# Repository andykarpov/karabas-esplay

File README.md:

# Karabas ESPlay

A derivative pcb for the ESPlay micro project.

## Key differences:

- A bigger 3.2" ILI9341 display
- Silicone buttons
- Turbo buttons (C and D)

## Credits and license

This board is derived from [ESPlay micro](https://github.com/pebri86/esplay_micro_hardware) by Fuji Pebri. That repository has no license file, but its author [states](https://github.com/pebri86/esplay_micro_hardware/issues/8) that the project is open source and free to modify and build upon, and asks to share modified versions.

The changes made in this repository are released under the MIT License, see [LICENSE](LICENSE). Rights in the original design remain with its author.

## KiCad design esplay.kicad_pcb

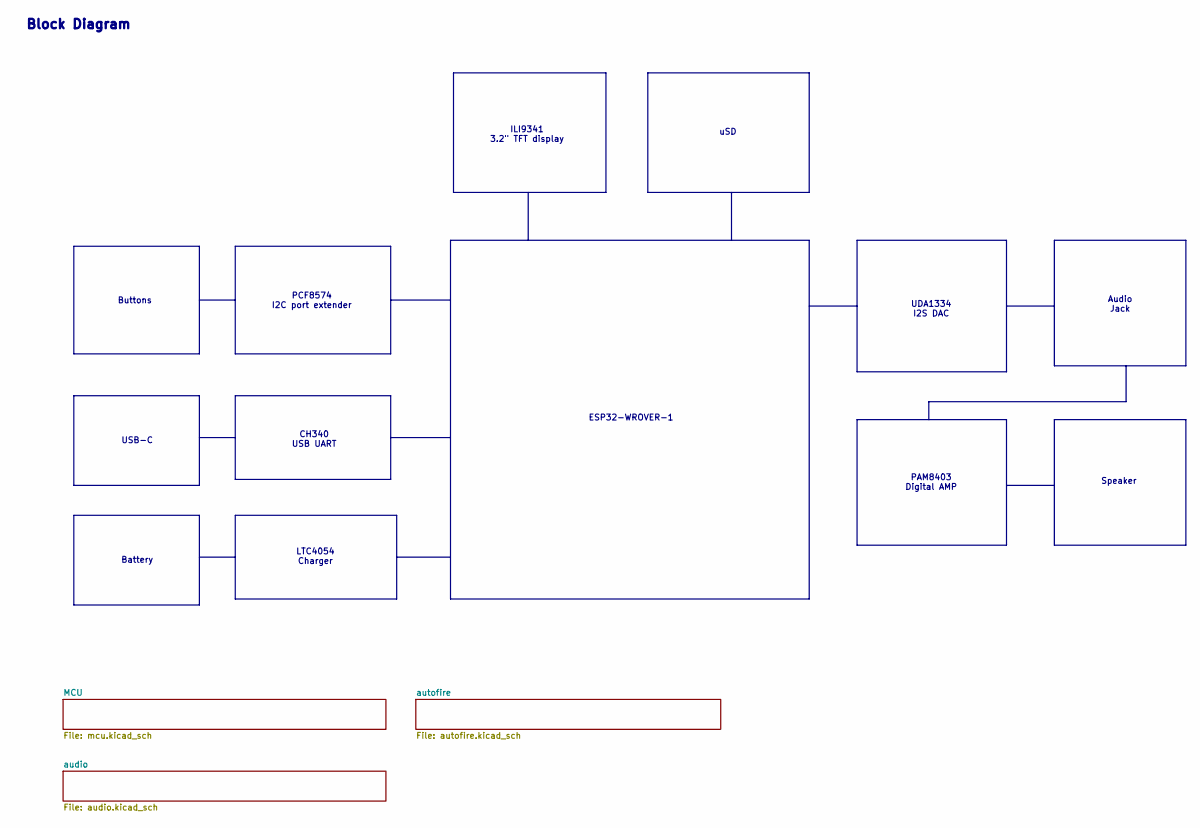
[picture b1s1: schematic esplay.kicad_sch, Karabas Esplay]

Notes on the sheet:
Block Diagram
PCF8574 I2C port extender
Audio Jack
uSD
Battery
LTC4054 Charger
UDA1334 I2S DAC
CH340 USB UART
Speaker
ILI9341 3.2" TFT display
Buttons
ESP32-WROVER-1
PAM8403 Digital AMP
USB-C

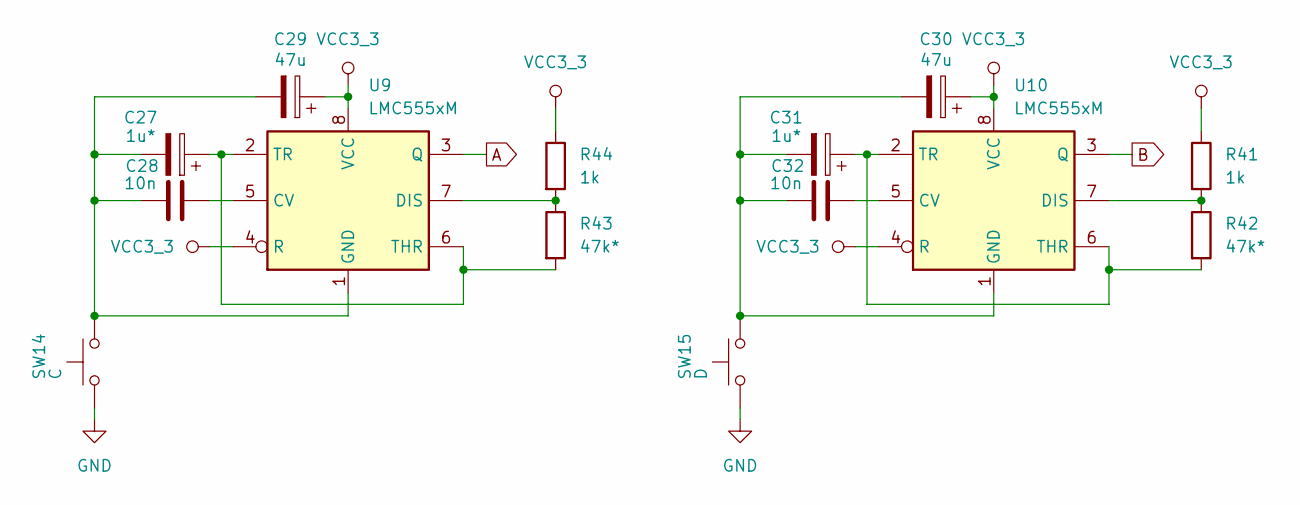
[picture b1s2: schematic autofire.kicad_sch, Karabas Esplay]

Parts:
C27, C31: 1u*; CP_EIA-3528-21_Kemet-B_HandSolder
C28, C32: 10n; C_0805_2012Metric_Pad1.18x1.45mm_HandSolder
C29, C30: 47u; CP_EIA-3528-21_Kemet-B_HandSolder
R41, R44: 1k; R_0805_2012Metric_Pad1.20x1.40mm_HandSolder
R42, R43: 47k*; R_0805_2012Metric_Pad1.20x1.40mm_HandSolder
SW14: C; SW_Push_1TS009_combined1
SW15: D; SW_Push_1TS009_combined1
U9, U10: LMC555xM; SOIC-8_3.9x4.9mm_P1.27mm

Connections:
A: U9.3 (Q); also elsewhere on the board
B: U10.3 (Q); also elsewhere on the board
GND: SW14.1, SW15.1; also elsewhere on the board
unnamed: C28.2, U9.5 (CV)
unnamed: R43.1, R44.2, U9.7 (DIS)
unnamed: C27.2, C28.1, C29.2, SW14.2, U9.1 (GND)
unnamed: C27.1, R43.2, U9.2 (TR), U9.6 (THR)
unnamed: C32.2, U10.5 (CV)
unnamed: R41.2, R42.1, U10.7 (DIS)
unnamed: C30.2, C31.2, C32.1, SW15.2, U10.1 (GND)
unnamed: C31.1, R42.2, U10.2 (TR), U10.6 (THR)
VCC3_3: C29.1, C30.1, R41.1, R44.1, U9.4 (R), U9.8 (VCC), U10.4 (R), U10.8 (VCC); also elsewhere on the board

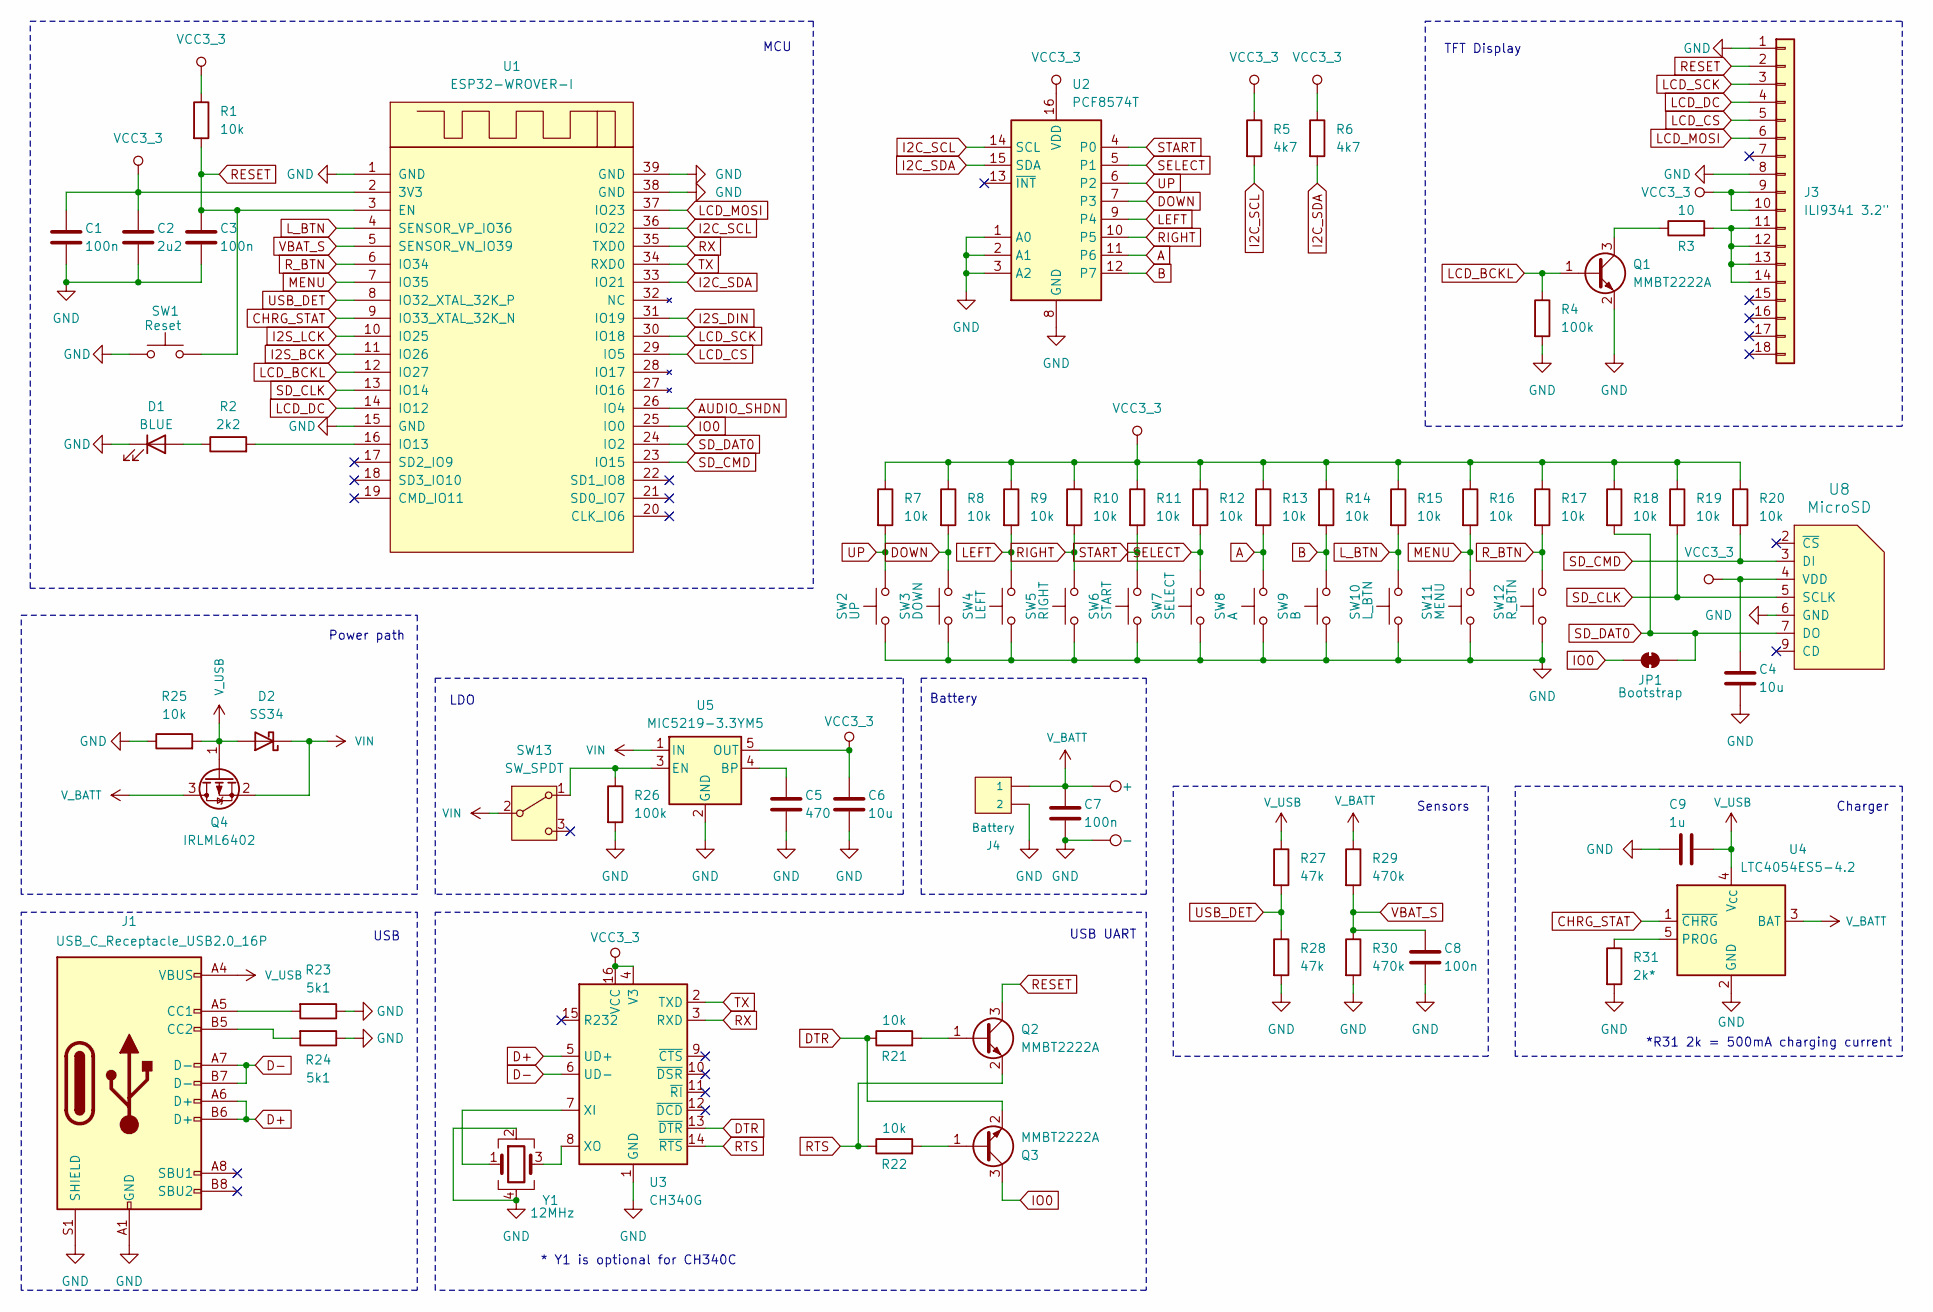
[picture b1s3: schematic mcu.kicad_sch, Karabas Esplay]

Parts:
BAT+1: +; TestPoint_Pad_D3.0mm
BAT-1: -; TestPoint_Pad_D3.0mm
C1, C3, C7, C8: 100n; C_0805_2012Metric_Pad1.18x1.45mm_HandSolder
C2: 2u2; C_0805_2012Metric_Pad1.18x1.45mm_HandSolder
C4, C6: 10u; C_0805_2012Metric_Pad1.18x1.45mm_HandSolder
C5: 470; C_0805_2012Metric_Pad1.18x1.45mm_HandSolder
C9: 1u; C_0805_2012Metric_Pad1.18x1.45mm_HandSolder
D1: BLUE; LED_0805_2012Metric_Pad1.15x1.40mm_HandSolder
D2: SS34; D_SMA
J1: USB_C_Receptacle_USB2.0_16P; USB_C_Receptacle_HRO_TYPE-C-31-M-12
J3: ILI9341 3.2"; TFT-ILI9341-3.2
J4: Battery; JST_PH_S2B-PH-K_1x02_P2.00mm_Horizontal
JP1: Bootstrap; SolderJumper-2_P1.3mm_Bridged_RoundedPad1.0x1.5mm
Q1, Q2, Q3: MMBT2222A; SOT-23
Q4: IRLML6402; SOT-23
R1, R7, R8, R9, R10, R11, R12, R13, R14, R15, R16, R17, R18, R19, R20, R21, R22, R25: 10k; R_0805_2012Metric_Pad1.20x1.40mm_HandSolder
R2: 2k2; R_0805_2012Metric_Pad1.20x1.40mm_HandSolder
R3: 10; R_0805_2012Metric_Pad1.20x1.40mm_HandSolder
R4, R26: 100k; R_0805_2012Metric_Pad1.20x1.40mm_HandSolder
R5, R6: 4k7; R_0805_2012Metric_Pad1.20x1.40mm_HandSolder
R23, R24: 5k1; R_0805_2012Metric_Pad1.20x1.40mm_HandSolder
R27, R28: 47k; R_0805_2012Metric_Pad1.20x1.40mm_HandSolder
R29, R30: 470k; R_0805_2012Metric_Pad1.20x1.40mm_HandSolder
R31: 2k*; R_0805_2012Metric_Pad1.20x1.40mm_HandSolder
SW1: Reset; SW_SPST_PTS810_handsoldering
SW2: UP; SW_Push_1TS009_combined1
SW3: DOWN; SW_Push_1TS009_combined1
SW4: LEFT; SW_Push_1TS009_combined1
SW5: RIGHT; SW_Push_1TS009_combined1
SW6: START; SW_Push_1TS009_combined1
SW7: SELECT; SW_Push_1TS009_combined1
SW8: A; SW_Push_1TS009_combined1
SW9: B; SW_Push_1TS009_combined1
SW10: L_BTN; SW_Tactile_SPST_Angled_PTS645Vx58-2LFS
SW11: MENU; SW_Push_1TS009_combined1
SW12: R_BTN; SW_Tactile_SPST_Angled_PTS645Vx58-2LFS
SW13: SW_SPDT; SW_Slide_SPDT_Angled_CK_OS102011MA1Q
U1: ESP32-WROVER-I; ESP32-WROVER
U2: PCF8574T; SOIC-16W_7.5x10.3mm_P1.27mm
U3: CH340G; SOIC-16_3.9x9.9mm_P1.27mm
U4: LTC4054ES5-4.2; TSOT-23-5
U5: MIC5219-3.3YM5; SOT-23-5
U8: MicroSD; GCT-MEM2055-00-190-01-A
Y1: 12MHz; Crystal_SMD_3225-4Pin_3.2x2.5mm_HandSoldering

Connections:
A: R13.2, SW8.2, U2.11 (P6); also elsewhere on the board
AUDIO_SHDN: U1.26 (IO4); also elsewhere on the board
B: R14.2, SW9.2, U2.12 (P7); also elsewhere on the board
CHRG_STAT: U1.9 (IO33_XTAL_32K_N), U4.1 (~CHRG)
D+: J1.A6 (D+), J1.B6 (D+), U3.5 (UD+)
D-: J1.A7 (D-), J1.B7 (D-), U3.6 (UD-)
DOWN: R8.2, SW3.2, U2.7 (P3)
DTR: Q3.2 (E), R21.1, U3.13 (~DTR)
GND: BAT-1.1, C1.2, C2.2, C3.2, C4.2, C5.2, C6.2, C7.2, C8.2, C9.1, D1.1 (K), J1.A1 (GND), J1.A12 (GND), J1.B1 (GND), J1.B12 (GND), J1.S1 (SHIELD), J3.1, J3.8, J4.2, Q1.2 (E), R4.2, R23.1, R24.1, R25.1, R26.2, R28.2, R30.2, R31.2, SW1.1, SW2.1, SW3.1, SW4.1, SW5.1, SW6.1, SW7.1, SW8.1, SW9.1, SW10.1, SW11.1, SW12.1, U1.1 (GND), U1.15 (GND), U1.38 (GND), U1.39 (GND), U2.1 (A0), U2.2 (A1), U2.3 (A2), U2.8 (GND), U3.1 (GND), U4.2 (GND), U5.2 (GND), U8.6 (GND), Y1.2, Y1.4; also elsewhere on the board
I2C_SCL: R5.2, U1.36 (IO22), U2.14 (SCL)
I2C_SDA: R6.2, U1.33 (IO21), U2.15 (SDA)
I2S_BCK: U1.11 (IO26); also elsewhere on the board
I2S_DIN: U1.31 (IO19); also elsewhere on the board
I2S_LCK: U1.10 (IO25); also elsewhere on the board
IO0: JP1.1 (A), Q3.3 (C), U1.25 (IO0)
LCD_BCKL: Q1.1 (B), R4.1, U1.12 (IO27)
LCD_CS: J3.5, U1.29 (IO5)
LCD_DC: J3.4, U1.14 (IO12)
LCD_MOSI: J3.6, U1.37 (IO23)
LCD_SCK: J3.3, U1.30 (IO18)
LEFT: R9.2, SW4.2, U2.9 (P4)
L_BTN: R15.2, SW10.2, U1.4 (SENSOR_VP_IO36)
MENU: R16.2, SW11.2, U1.7 (IO35)
unnamed: D1.2 (A), R2.1
unnamed: J1.A5 (CC1), R23.2
unnamed: J1.B5 (CC2), R24.2
unnamed: J3.11, J3.12, J3.13, J3.14, R3.2
unnamed: Q1.3 (C), R3.1
unnamed: Q2.1 (B), R21.2
unnamed: Q3.1 (B), R22.2
unnamed: R26.1, SW13.1 (A), U5.3 (EN)
unnamed: R2.2, U1.16 (IO13)
unnamed: U3.7 (XI), Y1.1
unnamed: U3.8 (XO), Y1.3
unnamed: R31.1, U4.5 (PROG)
unnamed: C5.1, U5.4 (BP)
RESET: C3.1, J3.2, Q2.3 (C), R1.2, SW1.2, U1.3 (EN)
RIGHT: R10.2, SW5.2, U2.10 (P5)
RTS: Q2.2 (E), R22.1, U3.14 (~RTS)
RX: U1.35 (TXD0), U3.3 (RXD)
R_BTN: R17.2, SW12.2, U1.6 (IO34)
SD_CLK: R19.2, U1.13 (IO14), U8.5 (SCLK)
SD_CMD: R20.2, U1.23 (IO15), U8.3 (DI)
SD_DAT0: JP1.2 (B), R18.2, U1.24 (IO2), U8.7 (DO)
SELECT: R12.2, SW7.2, U2.5 (P1)
START: R11.2, SW6.2, U2.4 (P0)
TX: U1.34 (RXD0), U3.2 (TXD)
UP: R7.2, SW2.2, U2.6 (P2)
USB_DET: R27.2, R28.1, U1.8 (IO32_XTAL_32K_P)
VBAT_S: C8.1, R29.2, R30.1, U1.5 (SENSOR_VN_IO39)
VCC3_3: C1.1, C2.1, C4.1, C6.1, J3.9, J3.10, R1.1, R5.1, R6.1, R7.1, R8.1, R9.1, R10.1, R11.1, R12.1, R13.1, R14.1, R15.1, R16.1, R17.1, R18.1, R19.1, R20.1, U1.2 (3V3), U2.16 (VDD), U3.4 (V3), U3.16 (VCC), U5.5 (OUT), U8.4 (VDD); also elsewhere on the board
VIN: D2.1 (K), Q4.2 (S), SW13.2 (B), U5.1 (IN); also elsewhere on the board
V_BATT: BAT+1.1, C7.1, J4.1, Q4.3 (D), R29.1, U4.3 (BAT)
V_USB: C9.2, D2.2 (A), J1.A4 (VBUS), J1.A9 (VBUS), J1.B4 (VBUS), J1.B9 (VBUS), Q4.1 (G), R25.2, R27.1, U4.4 (V_{CC})

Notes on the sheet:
*R31 2k = 500mA charging current
TFT Display
USB UART
USB
LDO
Charger
MCU
Battery
Sensors
* Y1 is optional for CH340C
Power path

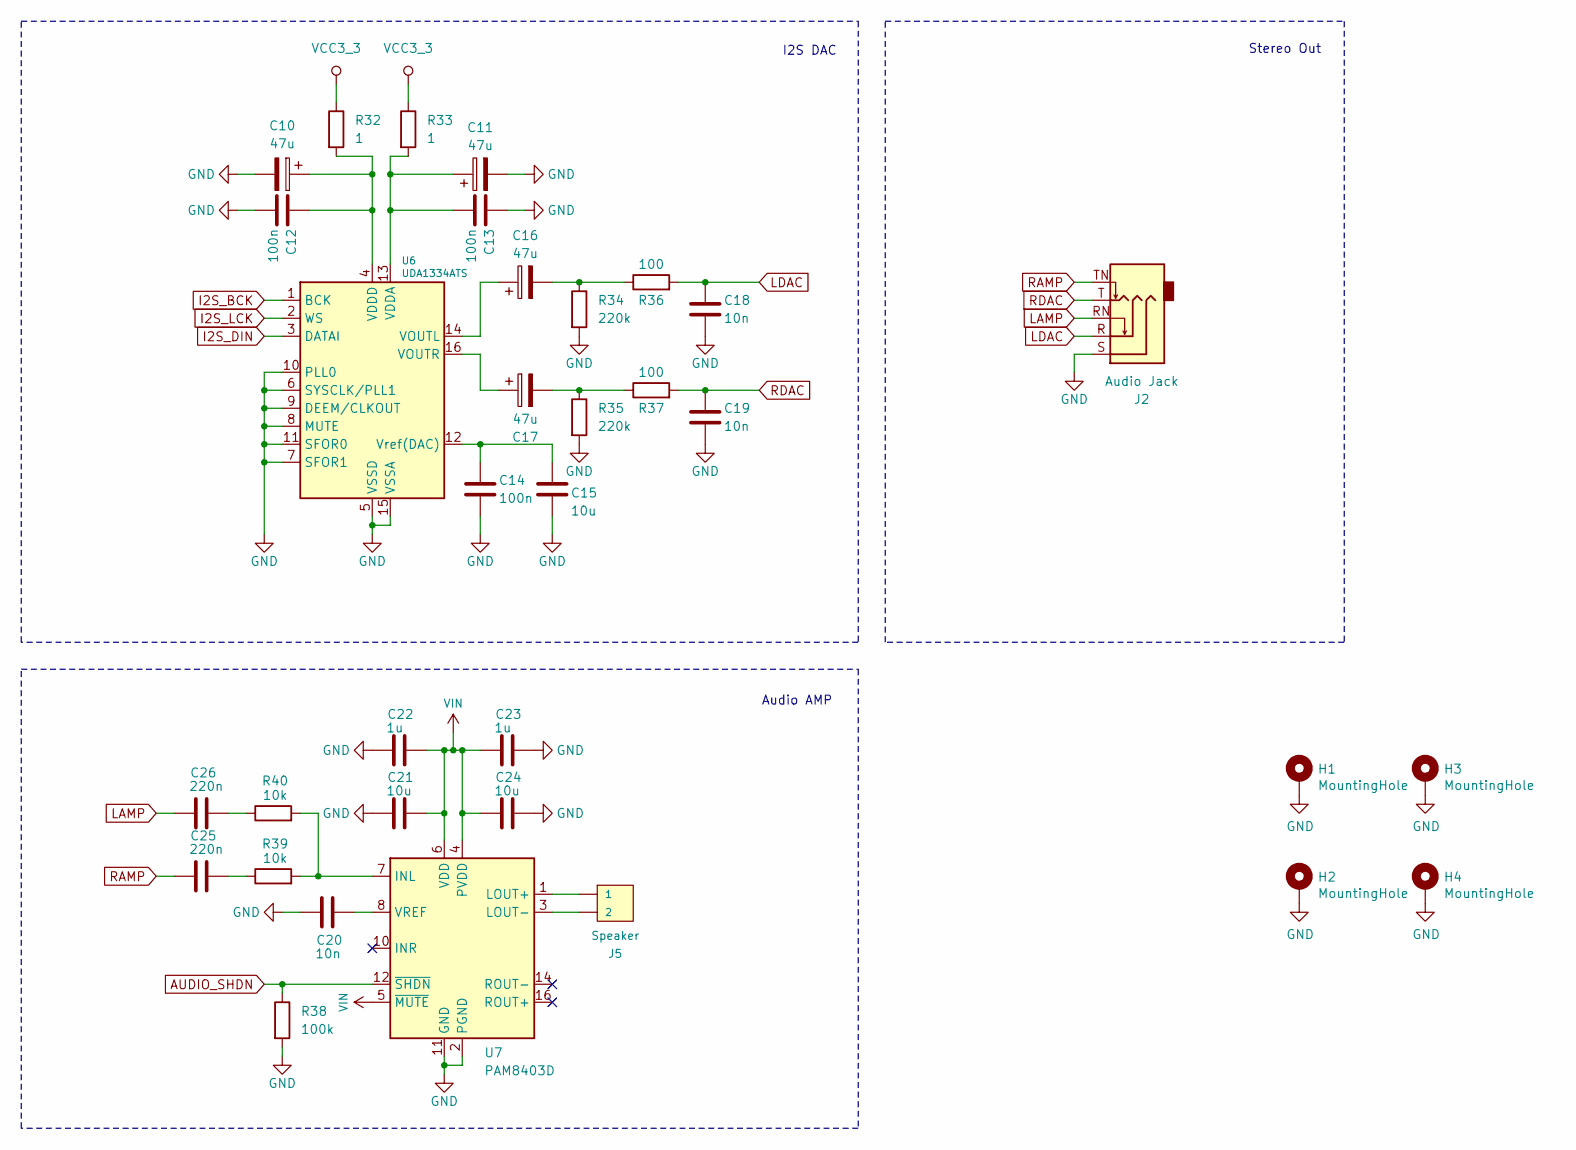
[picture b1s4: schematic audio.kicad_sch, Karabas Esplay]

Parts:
C10, C11, C16, C17: 47u; CP_EIA-3528-21_Kemet-B_HandSolder
C12, C13, C14: 100n; C_0805_2012Metric_Pad1.18x1.45mm_HandSolder
C15, C21, C24: 10u; C_0805_2012Metric_Pad1.18x1.45mm_HandSolder
C18, C19, C20: 10n; C_0805_2012Metric_Pad1.18x1.45mm_HandSolder
C22, C23: 1u; C_0805_2012Metric_Pad1.18x1.45mm_HandSolder
C25, C26: 220n; C_0805_2012Metric_Pad1.18x1.45mm_HandSolder
H1, H2, H3, H4: MountingHole; MountingHole_3.5mm_Pad_Via
J2: Audio Jack; Jack_3.5mm_CUI_SJ1-3525N_Horizontal
J5: Speaker; PinHeader_1x02_P2.54mm_Vertical
R32, R33: 1; R_0805_2012Metric_Pad1.20x1.40mm_HandSolder
R34, R35: 220k; R_0805_2012Metric_Pad1.20x1.40mm_HandSolder
R36, R37: 100; R_0805_2012Metric_Pad1.20x1.40mm_HandSolder
R38: 100k; R_0805_2012Metric_Pad1.20x1.40mm_HandSolder
R39, R40: 10k; R_0805_2012Metric_Pad1.20x1.40mm_HandSolder
U6: UDA1334ATS; SSOP-16_4.4x5.2mm_P0.65mm-extended
U7: PAM8403D; SOIC-16_3.9x9.9mm_P1.27mm

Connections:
AUDIO_SHDN: R38.1, U7.12 (~SHDN); also elsewhere on the board
GND: C10.2, C11.2, C12.2, C13.1, C14.2, C15.2, C18.2, C19.2, C20.1, C21.1, C22.1, C23.2, C24.2, H1.1, H2.1, H3.1, H4.1, J2.S, R34.2, R35.2, R38.2, U6.5 (VSSD), U6.6 (SYSCLK/PLL1), U6.7 (SFOR1), U6.8 (MUTE), U6.9 (DEEM/CLKOUT), U6.10 (PLL0), U6.11 (SFOR0), U6.15 (VSSA), U7.2 (PGND), U7.11 (GND), U7.15 (PGND); also elsewhere on the board
I2S_BCK: U6.1 (BCK); also elsewhere on the board
I2S_DIN: U6.3 (DATAI); also elsewhere on the board
I2S_LCK: U6.2 (WS); also elsewhere on the board
LAMP: C26.2, J2.RN
LDAC: C18.1, J2.R, R36.2
unnamed: C16.2, R34.1, R36.1
unnamed: C17.2, R35.1, R37.1
unnamed: C25.1, R39.1
unnamed: C26.1, R40.1
unnamed: C11.1, C13.2, R33.2, U6.13 (VDDA)
unnamed: C10.1, C12.1, R32.2, U6.4 (VDDD)
unnamed: C16.1, U6.14 (VOUTL)
unnamed: C17.1, U6.16 (VOUTR)
unnamed: C14.1, C15.1, U6.12 (Vref(DAC))
unnamed: R39.2, R40.2, U7.7 (INL)
unnamed: J5.1, U7.1 (LOUT+)
unnamed: J5.2, U7.3 (LOUT-)
unnamed: C20.2, U7.8 (VREF)
RAMP: C25.2, J2.TN
RDAC: C19.1, J2.T, R37.2
VCC3_3: R32.1, R33.1; also elsewhere on the board
VIN: C21.2, C22.2, C23.1, C24.1, U7.4 (PVDD), U7.5 (~MUTE), U7.6 (VDD), U7.13 (PVDD); also elsewhere on the board

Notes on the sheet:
Audio AMP
I2S DAC
Stereo Out

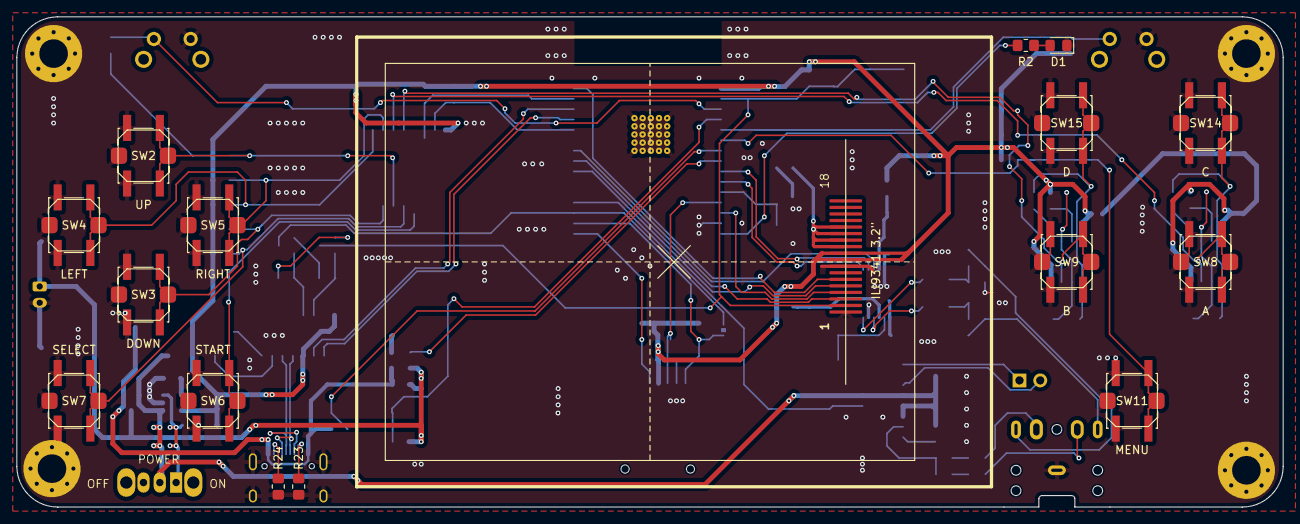
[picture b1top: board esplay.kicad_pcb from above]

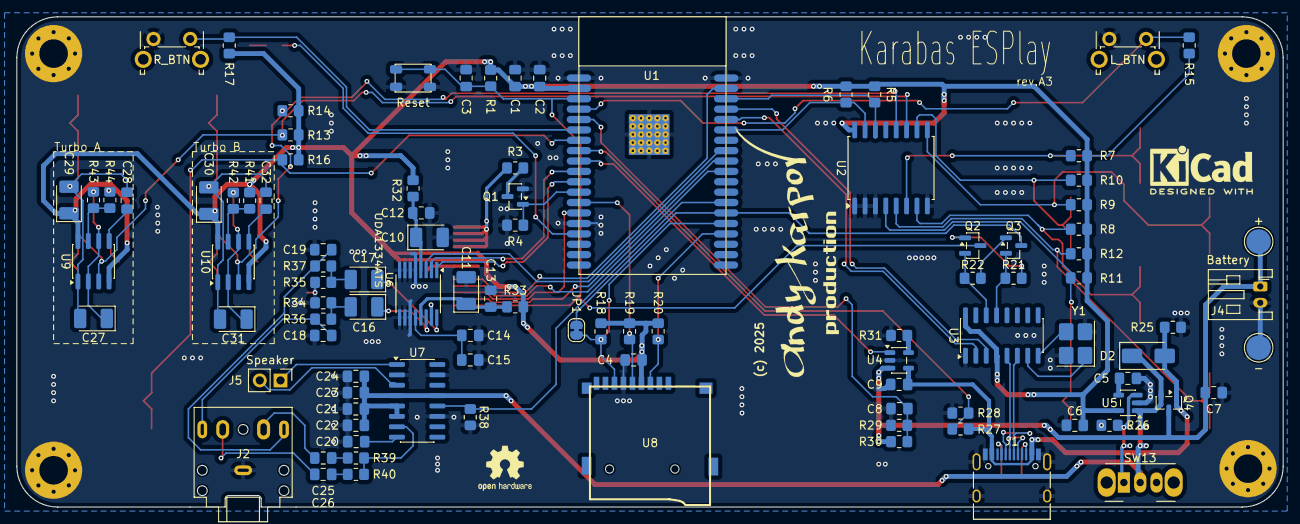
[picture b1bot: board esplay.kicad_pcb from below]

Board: 2 copper layers, 155.0 x 60.0 mm, 120 parts (100 on the bottom side), 79 nets.

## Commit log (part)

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2025-09-29 Final revA
2025-09-29 added keepout area to the wifi antenna
2025-09-30 Added revA2
2025-10-04 revA3
